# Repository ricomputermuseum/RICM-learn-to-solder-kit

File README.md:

# RICM-learn-to-solder-kit
These badges were designed as a soldering demo for the Rhode Island Computer Museum (RICM). They were designed to teach the basics of thru-hole soldering, as well as to provide users with a take home wearable. 
 
## Goals for this kit:
* A beginner kit for learning to solder.
* A simple circuit, 2 LEDS and a battery, but still interactive.
* Low cost, suitable for scout troops, school classes, summer camps, etc. Depending on order volume, parts will cost $2-4 per badge.

## Assembly instructions:
1. Solder the battery clip onto the exposed pads on the back of the board. Note that the battery clip used in this design is surface mount and considerably more difficult to solder than the other components. Depending on the audience it may be desirable for the instructor to solder this component before passing them out. 
2. Flip the board over and solder all other components to the front. Resistor values and transistor orientation are printed on the silkscreen.
3. Insert battery into clip and turn on switch. Hold hand over photoresistor to light up LEDS

## Parts list:
1x printed circuit board.
1x 47KΩ resistor (1/4W 5% carbon-film)
2x 220Ω resistors (1/4W 5% carbon-film)
1x NPN transistor (2N3904 or similar NPN (BC547,2N2222 etc.), TO-92-3 Kinked Lead)
2x light-emitting diodes (5mm, any color as desired)
1x SPDT mini slide switch (Shouhan SS-12D07VG3 or similar)
1x battery holder (Keystone 3002, 20mm coin cell, surface mount)
1x CR2032 Battery (3V, 20x3.2mm, 200mA)

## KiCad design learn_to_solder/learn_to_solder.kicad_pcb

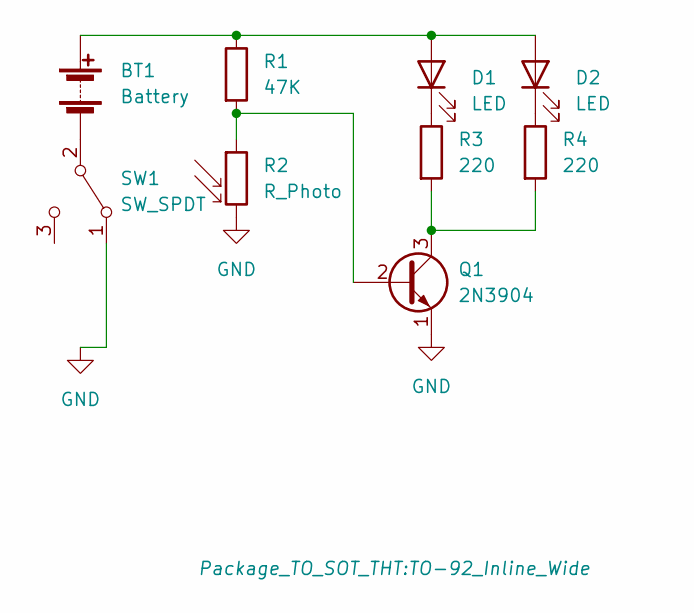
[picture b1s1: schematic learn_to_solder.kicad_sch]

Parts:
BT1: Battery; CR2032 retainer
D1, D2: LED; LED_D5.0mm
Q1: 2N3904; TO-92_Inline_Wide
R1: 47K; R_Axial_DIN0207_L6.3mm_D2.5mm_P10.16mm_Horizontal
R2: R_Photo; CP_Radial_Tantal_D4.5mm_P5.00mm
R3, R4: 220; R_Axial_DIN0207_L6.3mm_D2.5mm_P10.16mm_Horizontal
SW1: SW_SPDT; SW_Slide_1P2T_CK_OS102011MS2Q

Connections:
GND: Q1.1 (E), R2.2, SW1.1 (A)
unnamed: BT1.1 (+), D1.2 (A), D2.2 (A), R1.1
unnamed: BT1.2 (-), SW1.2 (B)
unnamed: D1.1 (K), R3.1
unnamed: D2.1 (K), R4.1
unnamed: Q1.2 (B), R1.2, R2.1
unnamed: Q1.3 (C), R3.2, R4.2

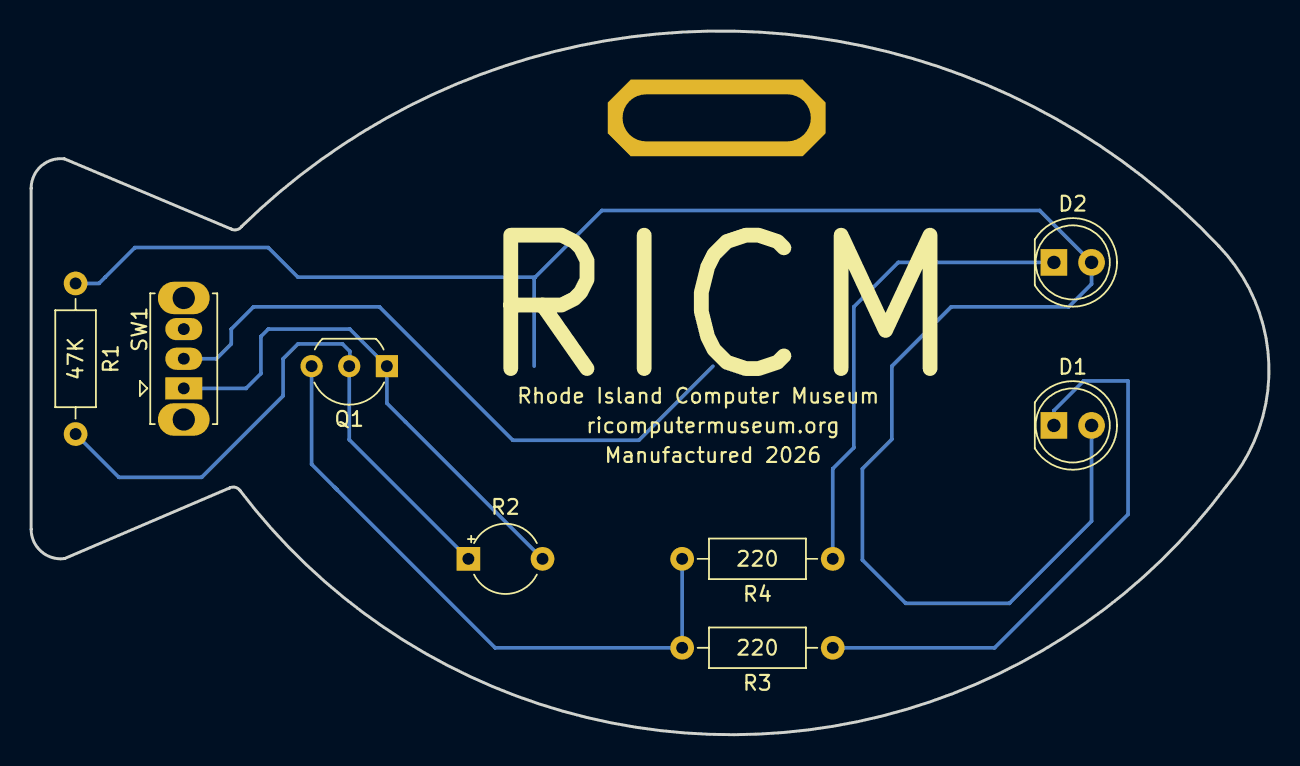
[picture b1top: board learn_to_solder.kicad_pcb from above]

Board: 2 copper layers, 83.5 x 47.5 mm, 9 parts (1 on the bottom side), 7 nets.

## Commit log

2023-09-08 Added kicad files for first draft
2023-09-09 Create README.md
    RICM Learn to Solder Badge
2023-09-09 Add files via upload
    RICM Badge Image
2023-09-22 plotted gerbers
2023-09-22 Updated readme and silkscreen
    Updated readme to correctly reflect kit components. Added labels in front silkscreen with resistor values to make assembly easier. Rearranged resistors to put both 220s next to each other.
2023-12-10 V2 updates
    Rearranged resistors to group both 220s together. Added slide switch to turn off without removing battery. Corrected typos in silkscreen. Fixed clip slot size.
2026-01-29 v3 edits
    Filleted sharp board edge. Added slot footprint for hanger.
